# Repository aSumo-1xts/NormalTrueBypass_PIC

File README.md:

<h1 align="center">
NormalTrueBypass_PIC
</h1>

<div align="center">

**A project for a true-bypass with an DIP8 PIC microcontroller.**

</div>

## Features

- Selectable operating mode: Alternate or Momentary
- Set the power-on state: ON or OFF
- (Option) Selectable timing to switch: when-pressed or when-released
- Automatically bypasses if power is accidentally turned off

## Verified on

- PIC12F629
- PIC12F675
- PIC12F1822

## dir: `KiCad`

KiCad関連のファイル一式です。

ガーバーファイルは[Release](https://github.com/asumo-1xts/NormalTrueBypass_PIC/releases)からダウンロードできます。

## dir: `src`

PICマイコン用のソースコード群です。

プロジェクト管理の様式はVScode用のMPLAB Extension Packに準拠しています。

コンパイル後のhexファイルは[Release](https://github.com/asumo-1xts/NormalTrueBypass_PIC/releases)からダウンロードできます。

PICマイコン間で共通のソースコードは`src`直下に、そうでないものはそのハードウェアの名前の付いたディレクトリに入っています。

`src/header.h`の冒頭で所望のPICマイコンのヘッダーファイルをincludeするだけで、そのPICマイコンが書き込み対象となります。

## `write_hex.*`

書き込みはコマンドラインで完結できます。

以下はPICKIT3でPIC12F675に書き込む際の例です。

### Debian 13 (and some other Linux distributions)

```shell
cd /opt/microchip/mplabx/v6.20/mplab_platform/mplab_ipe

sudo sh ipecmd.sh \
--% -P12F675 -TPPK3 -M \
-F"/home/asumo/Remote/NormalTrueBypass_PIC/out/PIC12F675/default.hex"
```

### Windows 11

```powershell
& "C:\Program Files\Microchip\MPLABX\v6.20\mplab_platform\mplab_ipe\ipecmd.exe" --% -P12F675 -TPPK3 -M -F"C:\Users\asumo\MPLABProjects\Lchica\out\Lchica\default.hex"
```

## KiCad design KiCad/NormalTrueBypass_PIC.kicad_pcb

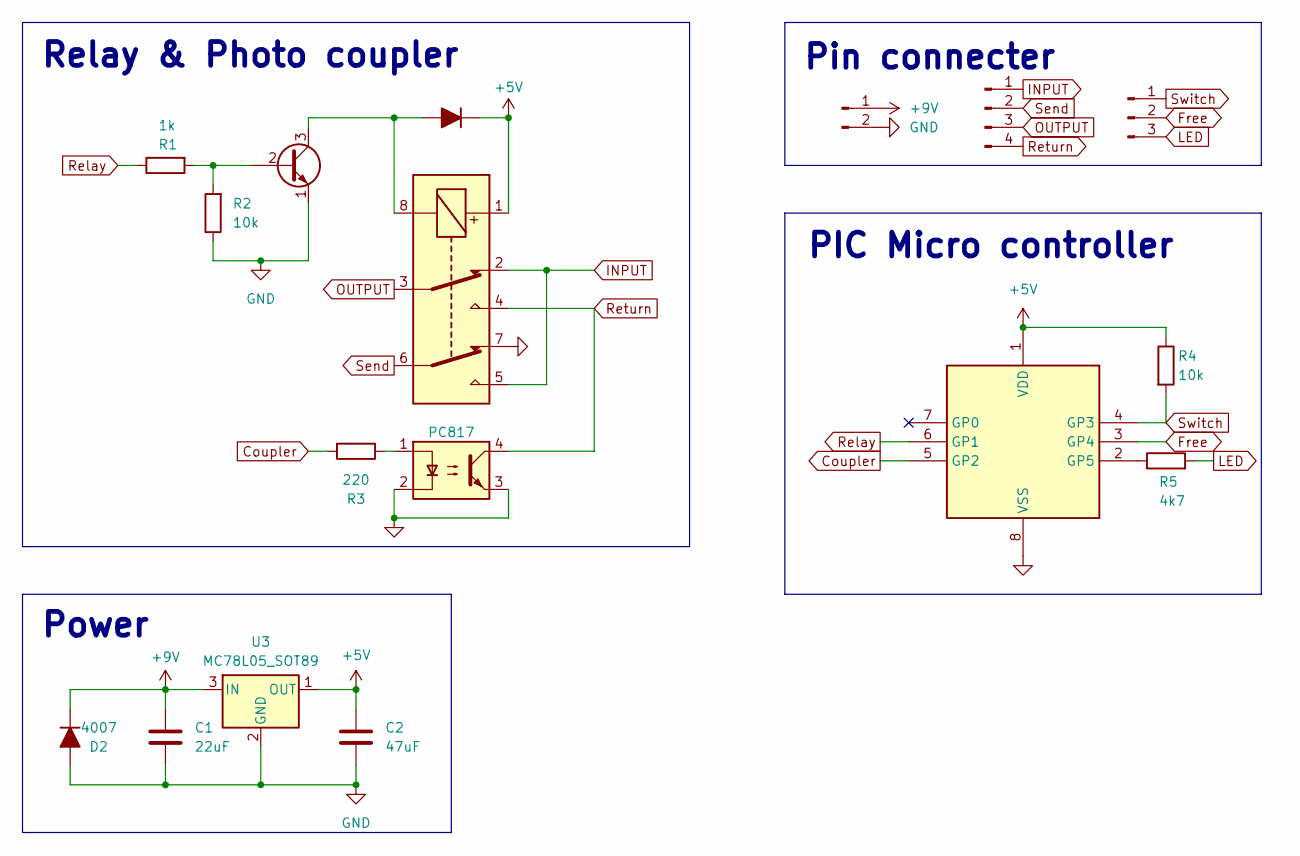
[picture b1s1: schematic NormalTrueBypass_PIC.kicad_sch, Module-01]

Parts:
C1: 22uF; C_0805_2012Metric
C2: 47uF; C_1206_3216Metric
D1: CD4148W; D_SOD-323
D2: 4007; D_SOD-323
J1: Conn_01x07_Pin; PinHeader_1x02_P2.54mm_Vertical
J2: Conn_01x07_Pin; PinHeader_1x04_P2.54mm_Vertical
J3: Conn_01x07_Pin; PinHeader_1x03_P2.54mm_Vertical
K1: Relay; Relay_DPDT_Omron_G6K-2G-Y
Q1: 2N3904; SOT-23
R1: 1k; R_0805_2012Metric
R2, R4: 10k; R_0805_2012Metric
R3: 220; R_0805_2012Metric
R5: 4k7; R_0805_2012Metric
U1: PC817; DIP-4_W7.62mm
U2: PIC12F675-xP; DIP-8_W7.62mm
U3: MC78L05_SOT89; SOT-89-3

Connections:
+5V: C2.1, D1.1 (K), K1.1, R4.1, U2.1 (VDD), U3.1 (OUT)
+9V: C1.1, D2.1 (K), J1.1, U3.3 (IN)
Coupler: R3.2, U2.5 (GP2)
Free: J3.2, U2.3 (GP4)
GND: C1.2, C2.2, D2.2 (A), J1.2, K1.7, Q1.1 (E), R2.1, U1.2, U1.3, U2.8 (VSS), U3.2 (GND)
INPUT: J2.1, K1.2, K1.5
LED: J3.3, R5.2
unnamed: D1.2 (A), K1.8, Q1.3 (C)
unnamed: Q1.2 (B), R1.2, R2.2
unnamed: R3.1, U1.1
unnamed: R5.1, U2.2 (GP5)
OUTPUT: J2.3, K1.3
Relay: R1.1, U2.6 (GP1)
Return: J2.4, K1.4, U1.4
Send: J2.2, K1.6
Switch: J3.1, R4.2, U2.4 (GP3)

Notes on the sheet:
Pin connecter
PIC Micro controller
Relay & Photo coupler
Power

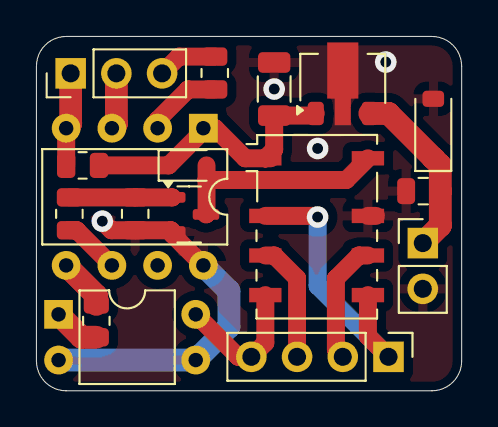
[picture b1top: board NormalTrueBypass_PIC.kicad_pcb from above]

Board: 2 copper layers, 23.6 x 19.7 mm, 17 parts (0 on the bottom side), 16 nets.

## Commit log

2025-03-31 add: KiCAD上のファイル3種を追加
2025-10-20 Deploying to doxygen from @ aSumo-1xts/NormalTrueBypass_PIC@319c0f437cce4b2e5673b091111f2f28e3625f9b 🚀
2025-10-20 Initial doxygen commit
2025-11-23 update: Immigrate from Win11 to Debian13
2025-11-23 update: write_hexコマンドを明示
2025-11-23 dev: From Win11 to Debian13 (#2)
    * update: Immigrate from Win11 to Debian13
    * update: write_hexコマンドを明示
2025-11-23 fix: フォトカプラの応答時間を修正
2025-11-23 fix: フォトカプラの応答時間を修正 (#4)
2025-11-23 Deploying to doxygen from @ asumo-1xts/NormalTrueBypass_PIC@e2291f73fc256a404ed85c26bdcff2f14aba204c 🚀
2025-11-23 auto: Format code
2025-11-23 Deploying to doxygen from @ asumo-1xts/NormalTrueBypass_PIC@6f5620c826c3fd0306de2e5605ebfa4585241414 🚀
2025-11-23 feat: 自動フォーマッタを導入
2025-11-23 feat: 自動フォーマッタを導入 (#5)
2025-11-23 Deploying to doxygen from @ asumo-1xts/NormalTrueBypass_PIC@b5bb8758efa4c23a4d91c13a7d922a769e548509 🚀
2025-11-23 fix: Actionsの発火条件を修正
2025-11-23 fix: Actionsの発火条件を修正 (#6)
2025-11-23 run: CI/CDを起こすためのコミット
2025-11-23 feat: 自動フォーマッタを導入 (#8)
2025-11-23 Deploying to doxygen from @ asumo-1xts/NormalTrueBypass_PIC@a9a593c1d4406c055afee05bb8bf507bc7827d11 🚀
2025-11-23 docs: READMEを編集
2025-11-23 docs: READMEを編集 (#9)
2025-11-24 docs: READMEを編集 (#11)
2025-11-24 delete: 不要な設定を削除
2025-11-24 delete: 不要な設定を削除 (#12)
2025-11-24 move: READMEをルートから移動
2025-11-24 move: READMEをルートから移動 (#13)
2025-12-10 move: .clang-formatを移動
2025-12-10 move: .clang-formatを移動 (#15)
2025-12-10 update: zsh-autoenvを導入
2025-12-12 move: .clang-formatをルートへ再移動
2025-12-12 update: 拡張機能に関する整備
2025-12-12 dev: 開発環境の整備 (#18)
    * move: .clang-formatをルートへ再移動
    * update: 拡張機能に関する整備
2025-12-18 feat: タスクランナーとしてmiseを導入
2025-12-18 feat: タスクランナーとしてmiseを導入 (#19)
2025-12-23 update: 英単語の前後の空白を削除
2025-12-23 add: 実際の基板の写真を追加
2025-12-23 docs: READMEを更新 (#20)
    * update: 英単語の前後の空白を削除
    * add: 実際の基板の写真を追加
2026-01-03 chore: Rename Actions-Bot
2026-01-03 chore: Change branch to deploy Doxygen
2026-01-03 docs: Update Doxygen documentation
2026-01-04 chore: Update VScode settings
2026-01-04 fix: Correct Doxygen directory
2026-01-11 chore: Rename format Action
2026-01-11 chore: Rename format Action (#1)
2026-01-11 docs: Edit README
2026-01-11 chore: Update and merge Actions
2026-01-11 chore: Update Clang-Format details
2026-01-16 chore: Merge three Actions
2026-01-21 docs: Delete all
2026-01-21 chore: Undeploy `docs/` and Simplify Action
2026-01-21 feat: Add `.ps1` script to write `*.hex`
2026-01-21 chore: Move doxygen-css from root
